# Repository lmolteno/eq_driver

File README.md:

# EQ Driver
## EQ3
Gear ratios:
RA seems to be about 5.46875:1 from the stepper to the worm, then the worm is about 130:1 (according to what I've read).

RA Stepper:
Big Gear: 66 teeth
interfaces with Stepper motor: 12 teeth

Big gear is attached to 35 teeth gear.
This is attached to another 35 tooth gear.
Total ratio is 66:12

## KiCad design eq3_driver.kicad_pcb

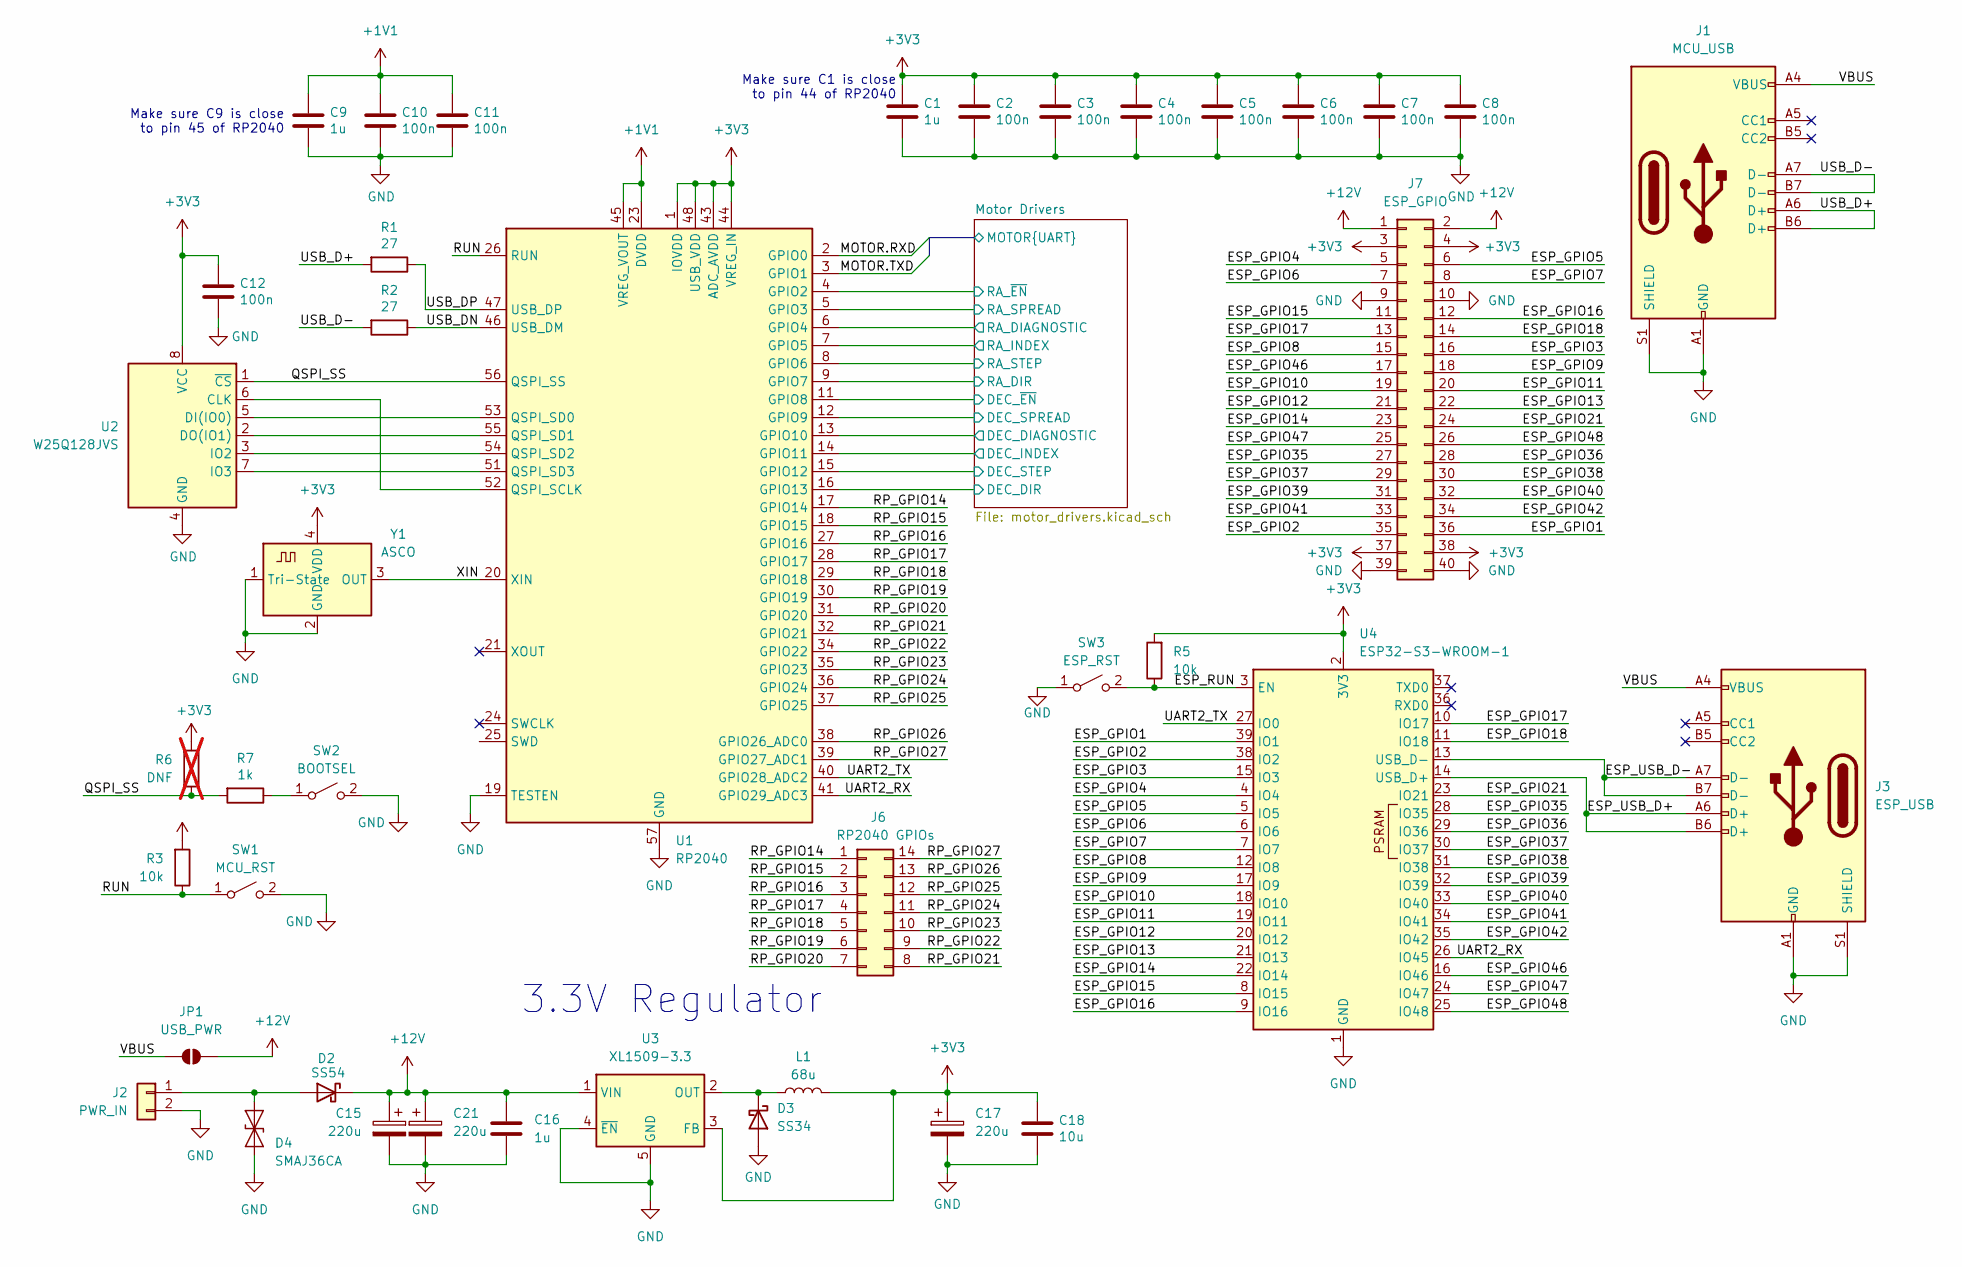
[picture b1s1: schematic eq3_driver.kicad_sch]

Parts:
C1, C9: 1u; C_0402_1005Metric; LCSC C52923
C2, C3, C4, C5, C6, C7, C8, C10, C11, C12: 100n; C_0402_1005Metric; LCSC C1525
C15, C21: 220u; C_Elec_6.3x7.7; LCSC C5246541
C16: 1u; C_0603_1608Metric; LCSC C15849
C17: 220u; CP_EIA-3528-21_Kemet-B; LCSC C30242
C18: 10u; C_0805_2012Metric; LCSC C15850
D2: SS54; D_SMA; LCSC C22452
D3: SS34; D_SMA; LCSC C8678
D4: SMAJ36CA; D_SMA; LCSC C87270
J1: MCU_USB; USB-C-TH_SHOUHAN_TYPE-C-14PLC-H10.0; LCSC C3151746
J2: PWR_IN; SolderWire-1sqmm_1x02_P5.4mm_D1.4mm_OD2.7mm
J3: ESP_USB; USB-C-TH_SHOUHAN_TYPE-C-14PLC-H10.0; LCSC C3151746
J6: RP2040 GPIOs; PinHeader_2x07_P2.00mm_Vertical
J7: ESP_GPIO; PinHeader_2x20_P2.00mm_Vertical
JP1: USB_PWR; SolderJumper-2_P1.3mm_Open_TrianglePad1.0x1.5mm
L1: 68u; L_Wuerth_WE-PD2-Typ-MS; LCSC C2929435
R1, R2: 27; R_0402_1005Metric; LCSC C25100
R3, R5: 10k; R_0402_1005Metric; LCSC C25744
R6: DNF; R_0402_1005Metric; LCSC C25744; not fitted
R7: 1k; R_0402_1005Metric; LCSC C11702
SW1: MCU_RST; SW-SMD_L3.9-W3.0-P4.45; LCSC C720477
SW2: BOOTSEL; SW-SMD_L3.9-W3.0-P4.45; LCSC C720477
SW3: ESP_RST; SW-SMD_L3.9-W3.0-P4.45; LCSC C720477
U1: RP2040; QFN-56-1EP_7x7mm_P0.4mm_EP3.2x3.2mm; LCSC C2040
U2: W25Q128JVS; SOIC-8_5.3x5.3mm_P1.27mm; LCSC C97521
U3: XL1509-3.3; SO-8_3.9x4.9mm_P1.27mm; LCSC C74193
U4: ESP32-S3-WROOM-1
Y1: ASCO; Crystal_SMD_5032-4Pin_5.0x3.2mm; LCSC C19674262

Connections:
+1V1: C9.1, C10.1, C11.1, U1.23 (DVDD), U1.45 (VREG_VOUT), U1.50 (DVDD)
+3V3: C1.1, C2.1, C3.1, C4.1, C5.1, C6.1, C7.1, C8.1, C12.1, C17.1, C18.1, J7.3, J7.4, J7.37, J7.38, L1.2, R3.2, R5.2, R6.2, U1.1 (IOVDD), U1.10 (IOVDD), U1.22 (IOVDD), U1.33 (IOVDD), U1.42 (IOVDD), U1.43 (ADC_AVDD), U1.44 (VREG_IN), U1.48 (USB_VDD), U1.49 (IOVDD), U2.8 (VCC), U3.3 (FB), U4.2 (3V3), Y1.4 (VDD); also elsewhere on the board
+12V: C15.1, C16.1, C21.1, D2.1 (K), J7.1, J7.2, JP1.2 (B), U3.1 (VIN); also elsewhere on the board
/ESP_GPIO1: J7.36, U4.39 (IO1)
/ESP_GPIO2: J7.35, U4.38 (IO2)
/ESP_GPIO3: J7.16, U4.15 (IO3)
/ESP_GPIO4: J7.5, U4.4 (IO4)
/ESP_GPIO5: J7.6, U4.5 (IO5)
/ESP_GPIO6: J7.7, U4.6 (IO6)
/ESP_GPIO7: J7.8, U4.7 (IO7)
/ESP_GPIO8: J7.15, U4.12 (IO8)
/ESP_GPIO9: J7.18, U4.17 (IO9)
/ESP_GPIO10: J7.19, U4.18 (IO10)
/ESP_GPIO11: J7.20, U4.19 (IO11)
/ESP_GPIO12: J7.21, U4.20 (IO12)
/ESP_GPIO13: J7.22, U4.21 (IO13)
/ESP_GPIO14: J7.23, U4.22 (IO14)
/ESP_GPIO15: J7.11, U4.8 (IO15)
/ESP_GPIO16: J7.12, U4.9 (IO16)
/ESP_GPIO17: J7.13, U4.10 (IO17)
/ESP_GPIO18: J7.14, U4.11 (IO18)
/ESP_GPIO21: J7.24, U4.23 (IO21)
/ESP_GPIO35: J7.27, U4.28 (IO35)
/ESP_GPIO36: J7.28, U4.29 (IO36)
/ESP_GPIO37: J7.29, U4.30 (IO37)
/ESP_GPIO38: J7.30, U4.31 (IO38)
/ESP_GPIO39: J7.31, U4.32 (IO39)
/ESP_GPIO40: J7.32, U4.33 (IO40)
/ESP_GPIO41: J7.33, U4.34 (IO41)
/ESP_GPIO42: J7.34, U4.35 (IO42)
/ESP_GPIO46: J7.17, U4.16 (IO46)
/ESP_GPIO47: J7.25, U4.24 (IO47)
/ESP_GPIO48: J7.26, U4.25 (IO48)
/ESP_RUN: R5.1, SW3.2 (B), U4.3 (EN)
/ESP_USB_D+: J3.A6 (D+), J3.B6 (D+), U4.14 (USB_D+)
/ESP_USB_D-: J3.A7 (D-), J3.B7 (D-), U4.13 (USB_D-)
/Motor Drivers/DEC_DIAGNOSTIC: U1.13 (GPIO10); also elsewhere on the board
/Motor Drivers/DEC_DIR: U1.16 (GPIO13); also elsewhere on the board
/Motor Drivers/DEC_INDEX: U1.14 (GPIO11); also elsewhere on the board
/Motor Drivers/DEC_SPREAD: U1.12 (GPIO9); also elsewhere on the board
/Motor Drivers/DEC_STEP: U1.15 (GPIO12); also elsewhere on the board
/Motor Drivers/DEC_~EN: U1.11 (GPIO8); also elsewhere on the board
/Motor Drivers/MOTOR.RXD: U1.2 (GPIO0); also elsewhere on the board
/Motor Drivers/MOTOR.TXD: U1.3 (GPIO1); also elsewhere on the board
/Motor Drivers/RA_DIAGNOSTIC: U1.6 (GPIO4); also elsewhere on the board
/Motor Drivers/RA_DIR: U1.9 (GPIO7); also elsewhere on the board
/Motor Drivers/RA_INDEX: U1.7 (GPIO5); also elsewhere on the board
/Motor Drivers/RA_SPREAD: U1.5 (GPIO3); also elsewhere on the board
/Motor Drivers/RA_STEP: U1.8 (GPIO6); also elsewhere on the board
/Motor Drivers/RA_~EN: U1.4 (GPIO2); also elsewhere on the board
/QSPI_SS: R6.1, R7.2, U1.56 (QSPI_SS), U2.1 (~CS)
/RP_GPIO14: J6.1, U1.17 (GPIO14)
/RP_GPIO15: J6.2, U1.18 (GPIO15)
/RP_GPIO16: J6.3, U1.27 (GPIO16)
/RP_GPIO17: J6.4, U1.28 (GPIO17)
/RP_GPIO18: J6.5, U1.29 (GPIO18)
/RP_GPIO19: J6.6, U1.30 (GPIO19)
/RP_GPIO20: J6.7, U1.31 (GPIO20)
/RP_GPIO21: J6.8, U1.32 (GPIO21)
/RP_GPIO22: J6.9, U1.34 (GPIO22)
/RP_GPIO23: J6.10, U1.35 (GPIO23)
/RP_GPIO24: J6.11, U1.36 (GPIO24)
/RP_GPIO25: J6.12, U1.37 (GPIO25)
/RP_GPIO26: J6.13, U1.38 (GPIO26_ADC0)
/RP_GPIO27: J6.14, U1.39 (GPIO27_ADC1)
/RUN: R3.1, SW1.1 (A), U1.26 (RUN)
/UART2_RX: U1.41 (GPIO29_ADC3), U4.26 (IO45)
/UART2_TX: U1.40 (GPIO28_ADC2), U4.27 (IO0)
/USB_D+: J1.A6 (D+), J1.B6 (D+), R1.2
/USB_D-: J1.A7 (D-), J1.B7 (D-), R2.2
/USB_DN: R2.1, U1.46 (USB_DM)
/USB_DP: R1.1, U1.47 (USB_DP)
/VBUS: J1.A4 (VBUS), J1.A9 (VBUS), J1.B4 (VBUS), J1.B9 (VBUS), J3.A4 (VBUS), J3.A9 (VBUS), J3.B4 (VBUS), J3.B9 (VBUS), JP1.1 (A)
/XIN: U1.20 (XIN), Y1.3 (OUT)
GND: C1.2, C2.2, C3.2, C4.2, C5.2, C6.2, C7.2, C8.2, C9.2, C10.2, C11.2, C12.2, C15.2, C16.2, C17.2, C18.2, C21.2, D3.2 (A), D4.1 (A1), J1.A1 (GND), J1.A12 (GND), J1.B1 (GND), J1.B12 (GND), J1.S1 (SHIELD), J2.2, J3.A1 (GND), J3.A12 (GND), J3.B1 (GND), J3.B12 (GND), J3.S1 (SHIELD), J7.9, J7.10, J7.39, J7.40, SW1.2 (B), SW2.2 (B), SW3.1 (A), U1.19 (TESTEN), U1.57 (GND), U2.4 (GND), U3.4 (~EN), U3.5 (GND), U3.6 (GND), U3.7 (GND), U3.8 (GND), U4.1 (GND), U4.40 (GND), U4.41 (GND), Y1.1 (Tri-State), Y1.2 (GND); also elsewhere on the board
unnamed: D2.2 (A), D4.2 (A2), J2.1
unnamed: D3.1 (K), L1.1, U3.2 (OUT)
unnamed: R7.1, SW2.1 (A)
unnamed: U1.52 (QSPI_SCLK), U2.6 (CLK)
unnamed: U1.53 (QSPI_SD0), U2.5 (DI(IO0))
unnamed: U1.55 (QSPI_SD1), U2.2 (DO(IO1))
unnamed: U1.54 (QSPI_SD2), U2.3 (IO2)
unnamed: U1.51 (QSPI_SD3), U2.7 (IO3)

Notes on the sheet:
Make sure C9 is close to pin 45 of RP2040
Make sure C1 is close to pin 44 of RP2040
3.3V Regulator

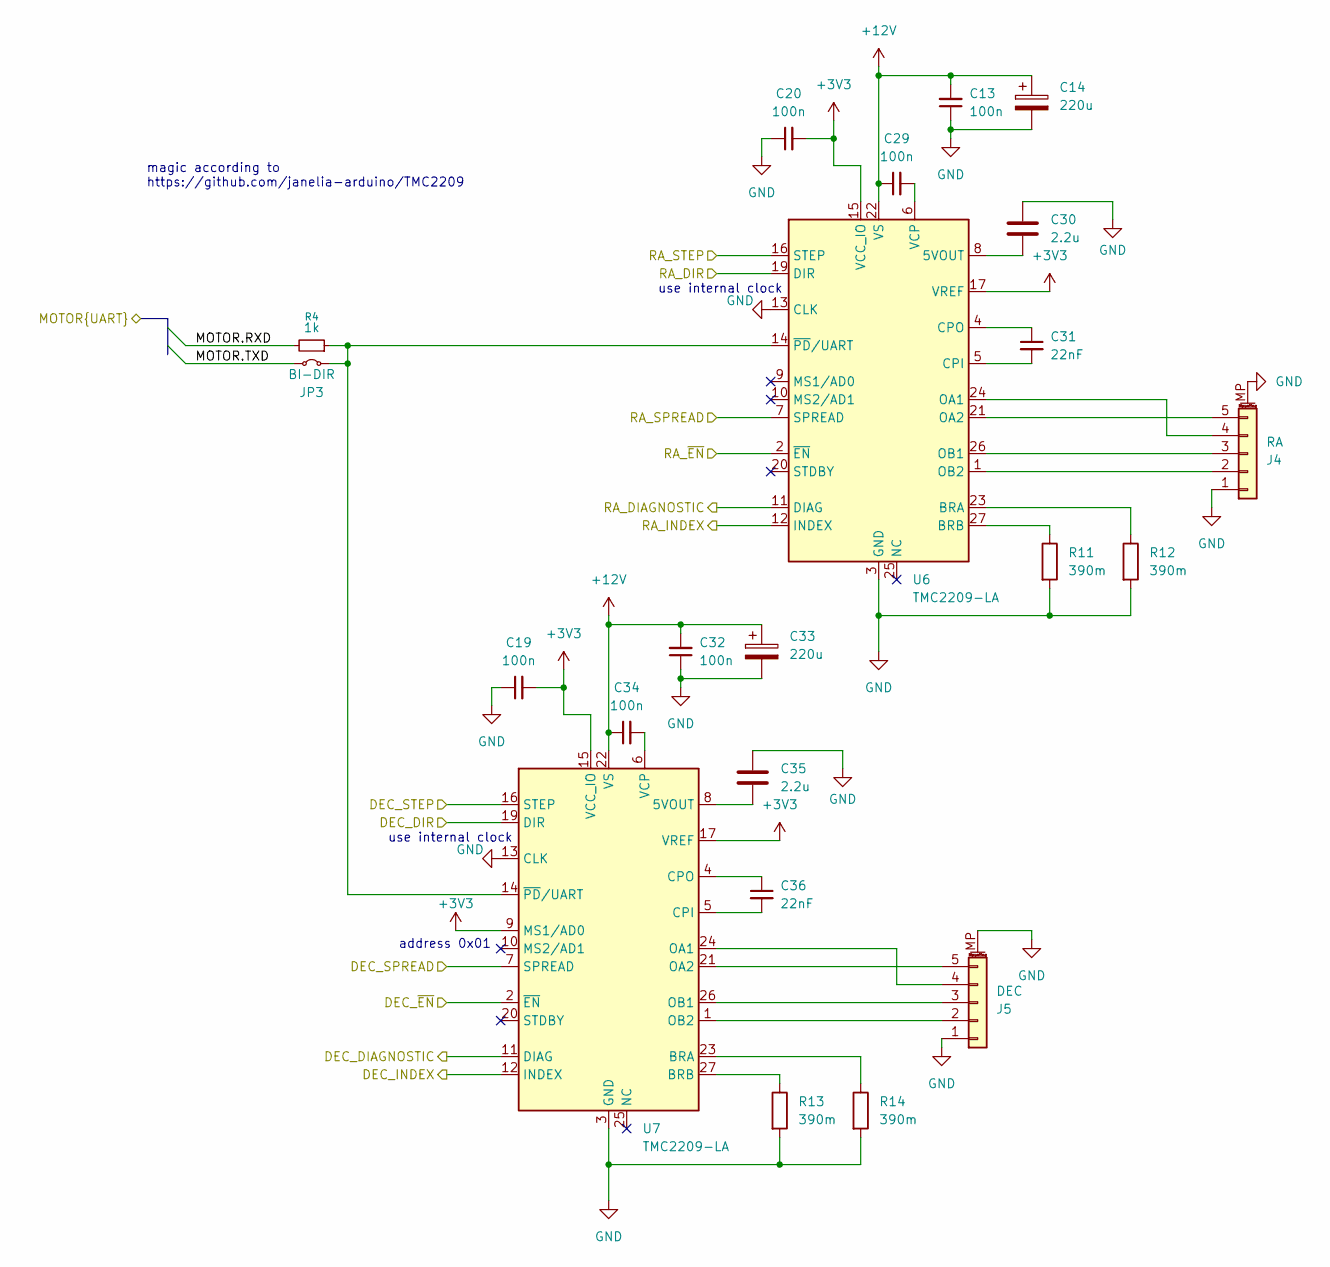
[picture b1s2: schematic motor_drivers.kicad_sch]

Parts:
C13, C19, C20, C29, C32, C34: 100n; C_0402_1005Metric; LCSC C1525
C14, C33: 220u; C_Elec_6.3x7.7; LCSC C5246541
C30, C35: 2.2u; C_0603_1608Metric; LCSC C23630
C31, C36: 22nF; C_0603_1608Metric; LCSC C21122
J4: RA; JST_PH_B5B-PH-SM4-TB_1x05-1MP_P2.00mm_Vertical; LCSC C265085
J5: DEC; JST_PH_B5B-PH-SM4-TB_1x05-1MP_P2.00mm_Vertical; LCSC C265085
JP3: BI-DIR; SolderJumper-2_P1.3mm_Bridged_RoundedPad1.0x1.5mm
R4: 1k; R_0402_1005Metric; LCSC C11702
R11, R12, R13, R14: 390m; R_1206_3216Metric; LCSC C188072
U6, U7: TMC2209-LA; VQFN-28-1EP_5x5mm_P0.5mm_EP3.7x3.7mm; LCSC C2150710

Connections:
+3V3: C19.2, C20.2, U6.15 (VCC_IO), U6.17 (VREF), U7.9 (MS1/AD0), U7.15 (VCC_IO), U7.17 (VREF); also elsewhere on the board
+12V: C13.2, C14.1, C29.1, C32.2, C33.1, C34.1, U6.22 (VS), U6.28 (VS), U7.22 (VS), U7.28 (VS); also elsewhere on the board
/Motor Drivers/DEC_DIAGNOSTIC: U7.11 (DIAG); also elsewhere on the board
/Motor Drivers/DEC_DIR: U7.19 (DIR); also elsewhere on the board
/Motor Drivers/DEC_INDEX: U7.12 (INDEX); also elsewhere on the board
/Motor Drivers/DEC_SPREAD: U7.7 (SPREAD); also elsewhere on the board
/Motor Drivers/DEC_STEP: U7.16 (STEP); also elsewhere on the board
/Motor Drivers/DEC_~EN: U7.2 (~EN); also elsewhere on the board
/Motor Drivers/MOTOR.RXD: R4.2; also elsewhere on the board
/Motor Drivers/MOTOR.TXD: JP3.2 (B); also elsewhere on the board
/Motor Drivers/RA_DIAGNOSTIC: U6.11 (DIAG); also elsewhere on the board
/Motor Drivers/RA_DIR: U6.19 (DIR); also elsewhere on the board
/Motor Drivers/RA_INDEX: U6.12 (INDEX); also elsewhere on the board
/Motor Drivers/RA_SPREAD: U6.7 (SPREAD); also elsewhere on the board
/Motor Drivers/RA_STEP: U6.16 (STEP); also elsewhere on the board
/Motor Drivers/RA_~EN: U6.2 (~EN); also elsewhere on the board
GND: C13.1, C14.2, C19.1, C20.1, C30.1, C32.1, C33.2, C35.1, J4.1, J4.MP (MountPin), J5.1, J5.MP (MountPin), R11.2, R12.2, R13.2, R14.2, U6.3 (GND), U6.13 (CLK), U6.18 (GND), U6.29 (GND), U7.3 (GND), U7.13 (CLK), U7.18 (GND), U7.29 (GND); also elsewhere on the board
unnamed: J4.2, U6.1 (OB2)
unnamed: J4.3, U6.26 (OB1)
unnamed: J4.4, U6.24 (OA1)
unnamed: J4.5, U6.21 (OA2)
unnamed: J5.2, U7.1 (OB2)
unnamed: J5.3, U7.26 (OB1)
unnamed: J5.4, U7.24 (OA1)
unnamed: J5.5, U7.21 (OA2)
unnamed: JP3.1 (A), R4.1, U6.14 (~PD/UART), U7.14 (~PD/UART)
unnamed: C30.2, U6.8 (5VOUT)
unnamed: R12.1, U6.23 (BRA)
unnamed: R11.1, U6.27 (BRB)
unnamed: C31.2, U6.5 (CPI)
unnamed: C31.1, U6.4 (CPO)
unnamed: C29.2, U6.6 (VCP)
unnamed: C35.2, U7.8 (5VOUT)
unnamed: R14.1, U7.23 (BRA)
unnamed: R13.1, U7.27 (BRB)
unnamed: C36.2, U7.5 (CPI)
unnamed: C36.1, U7.4 (CPO)
unnamed: C34.2, U7.6 (VCP)

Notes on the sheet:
address 0x01
magic according to https://github.com/janelia-arduino/TMC2209
use internal clock

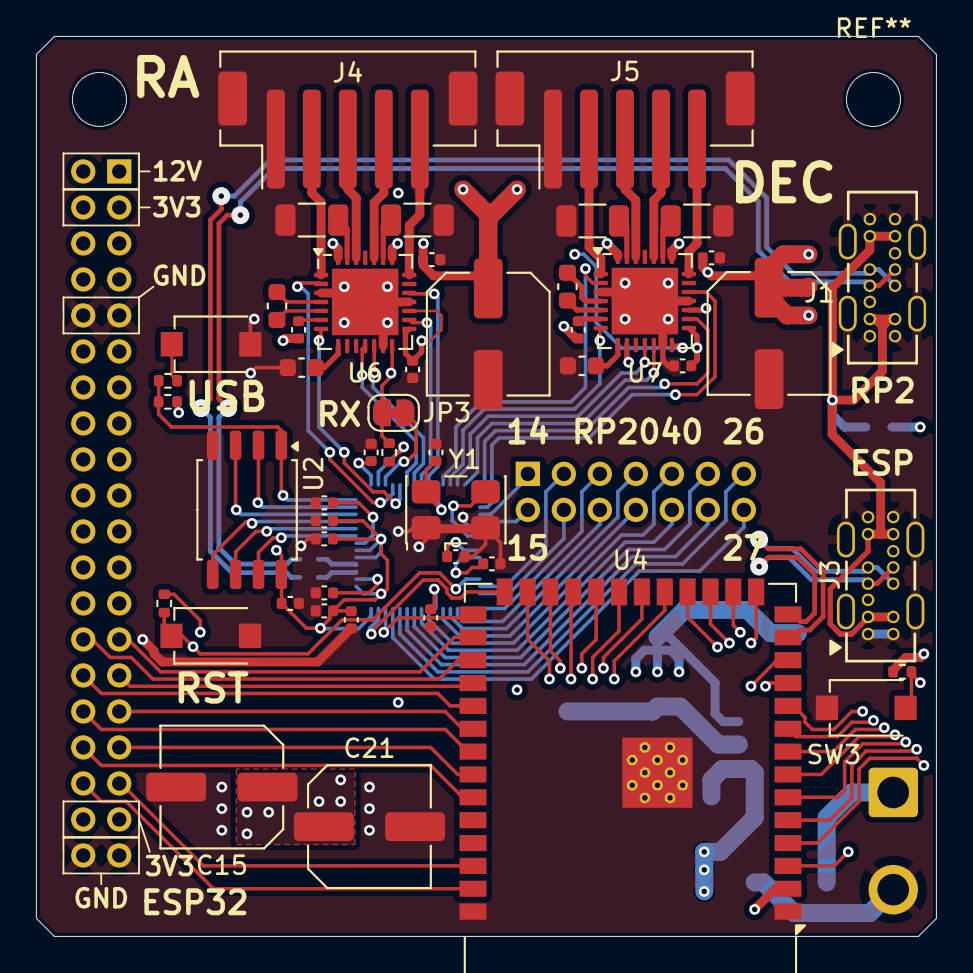
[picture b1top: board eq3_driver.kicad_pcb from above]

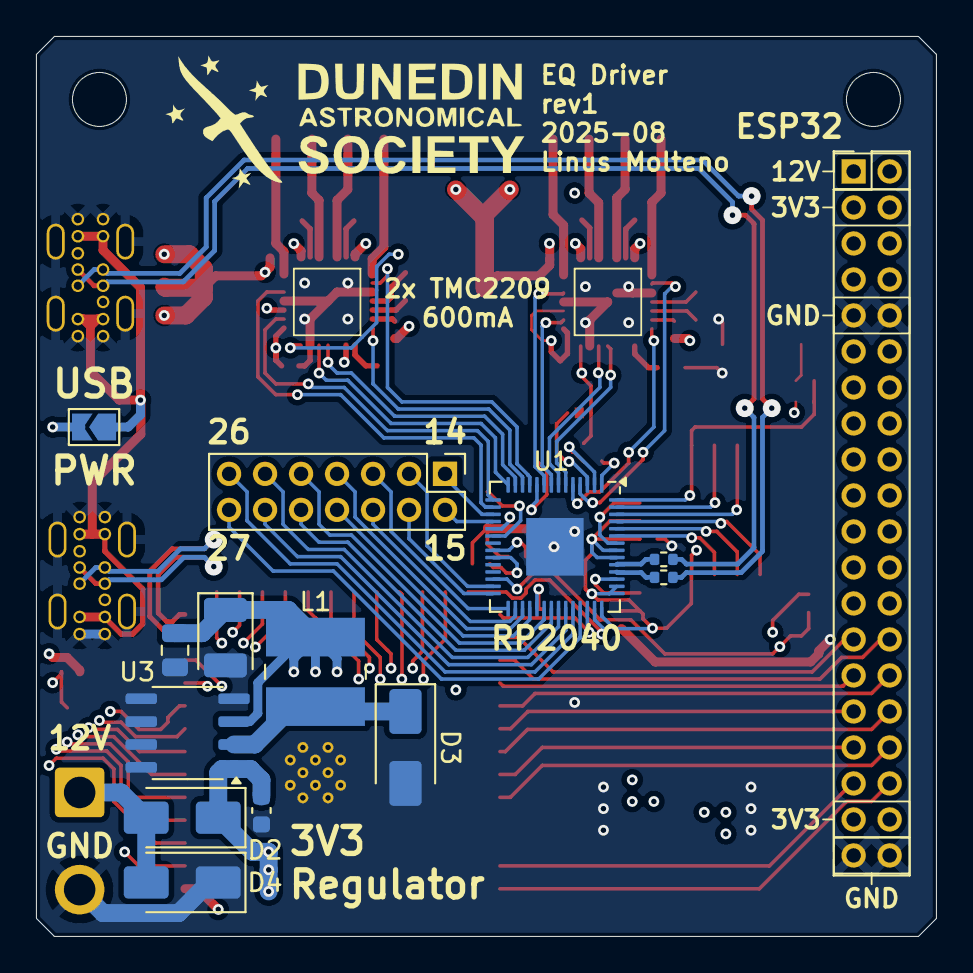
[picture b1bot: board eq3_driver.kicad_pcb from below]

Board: 4 copper layers, 50.0 x 50.0 mm, 63 parts (15 on the bottom side), 104 nets.

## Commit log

2025-09-18 feat: hardware
2025-09-18 feat: rp2040 firmware (pid control)
2025-09-19 chore: get comms between them
2025-09-19 chore: try to get bluetooth
2025-09-19 fix: push the right files
2025-09-20 feat: it works - just tweaking to float velocities.
2025-09-20 feat: full workflow going - established gear ratios
2025-09-21 chore: last changes until eclipse
